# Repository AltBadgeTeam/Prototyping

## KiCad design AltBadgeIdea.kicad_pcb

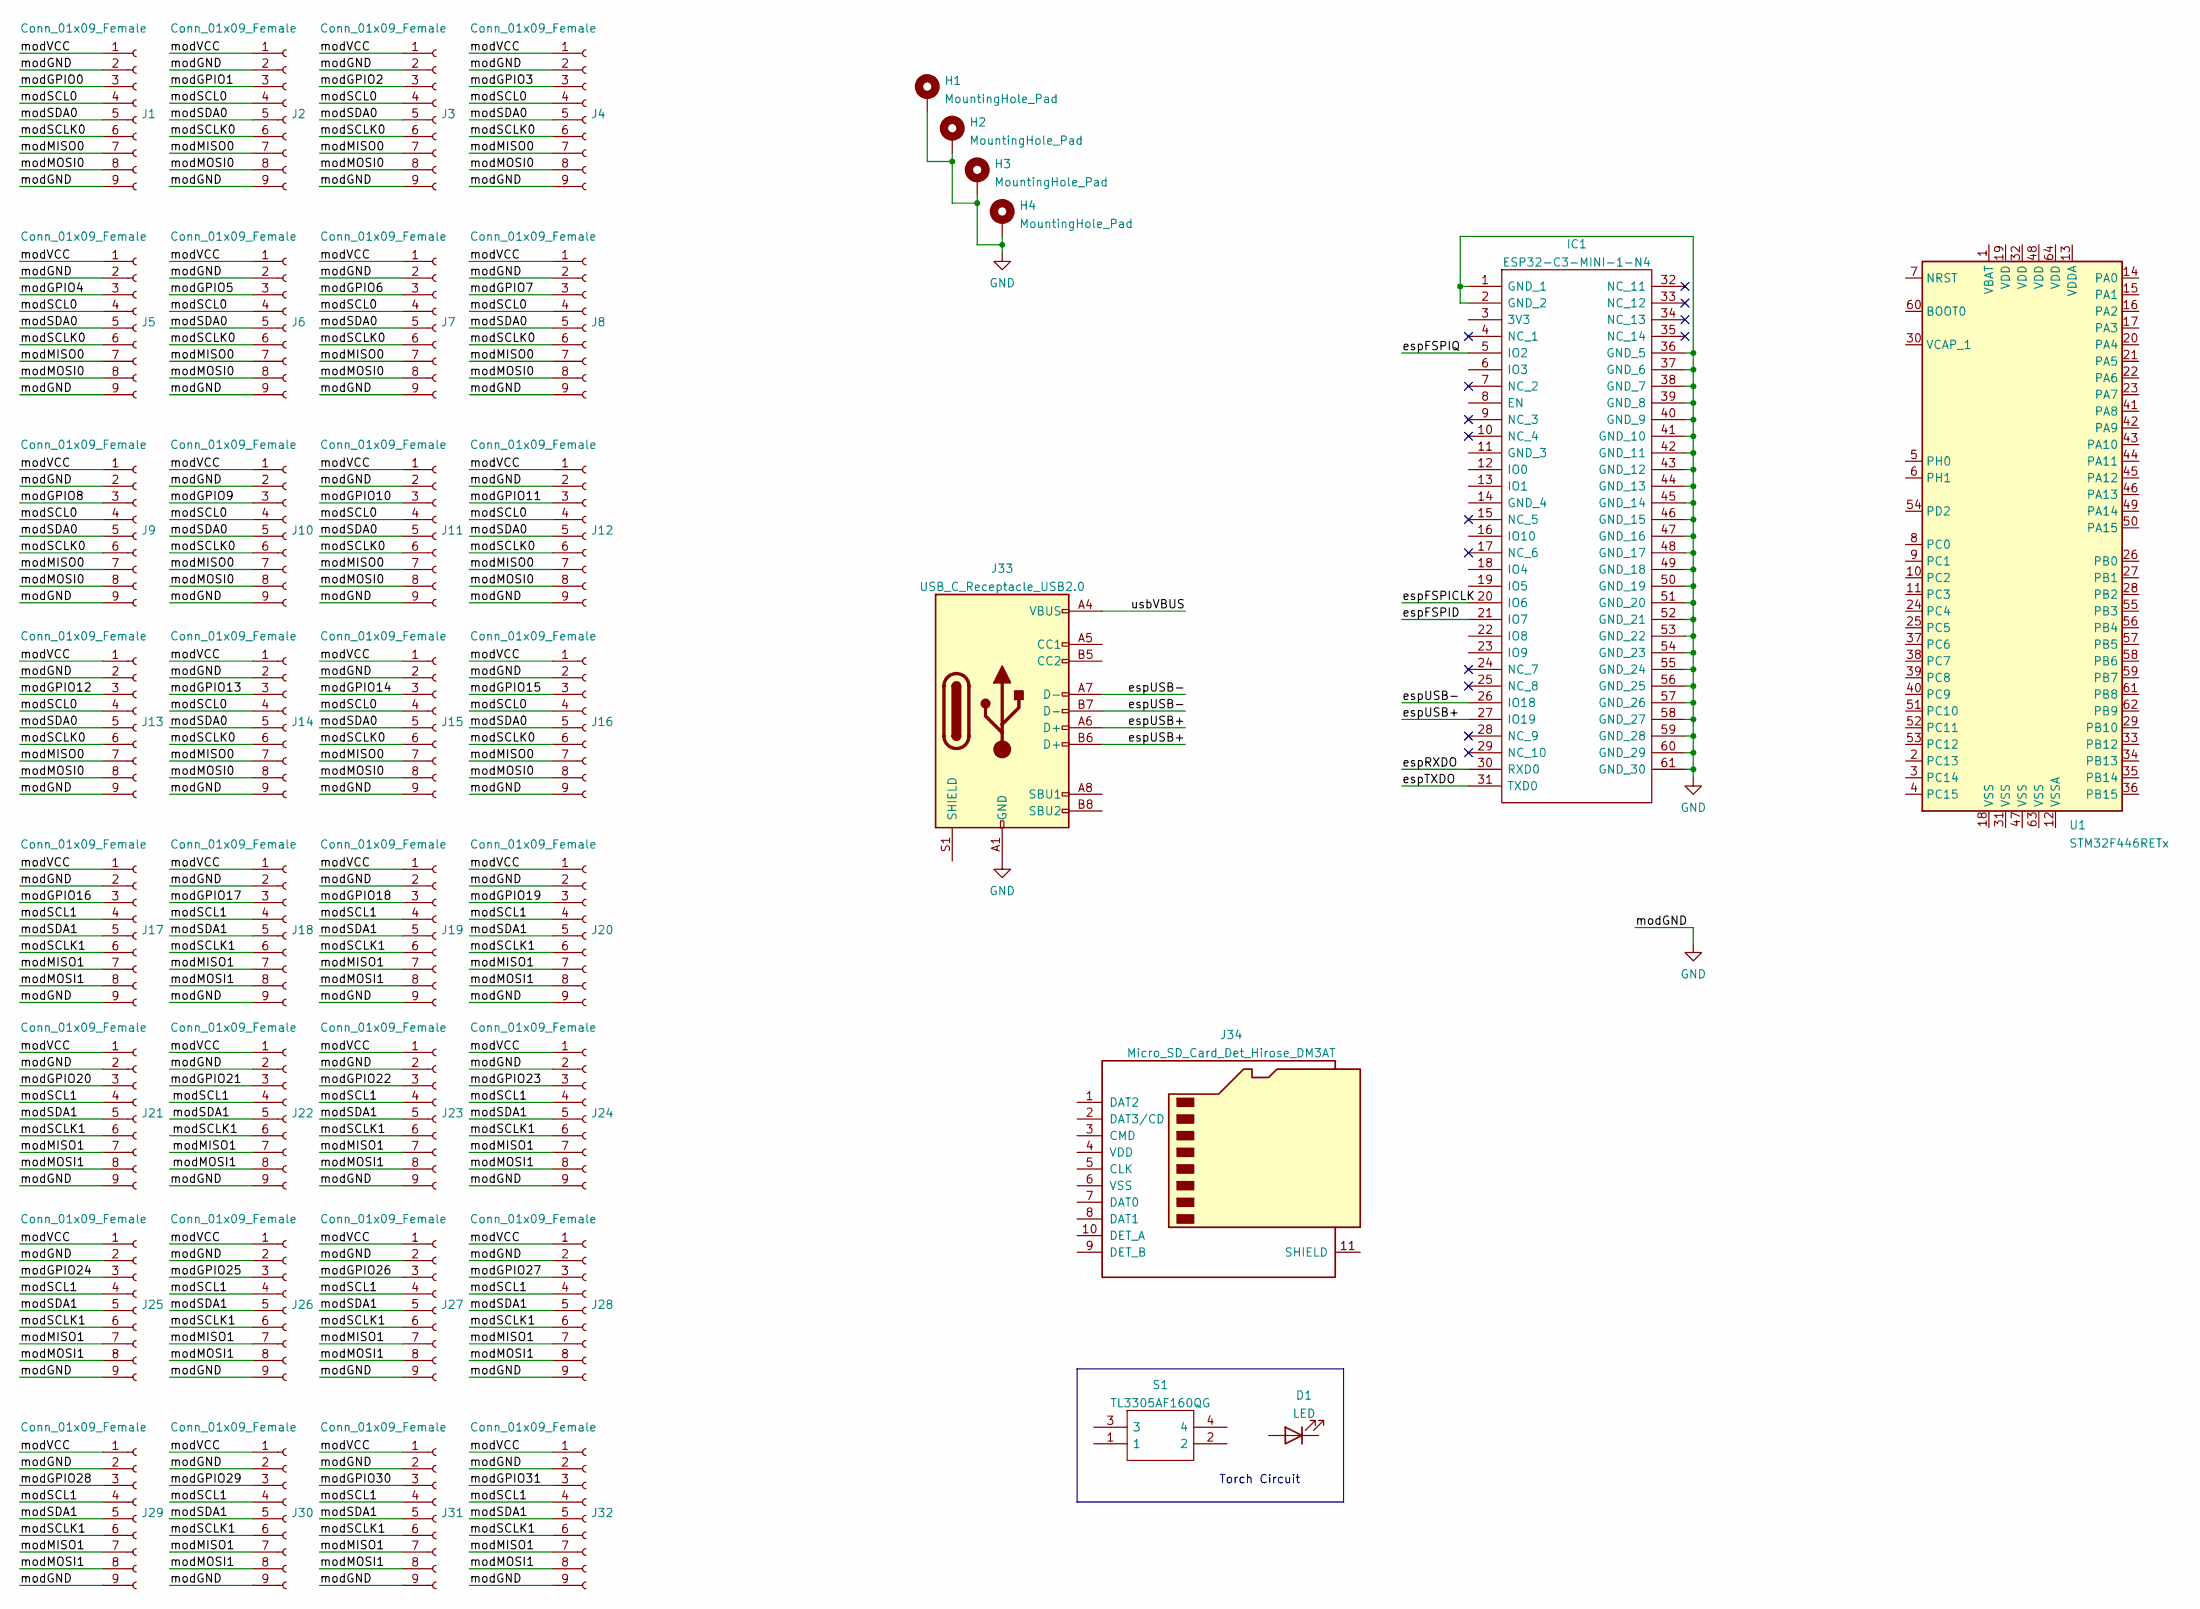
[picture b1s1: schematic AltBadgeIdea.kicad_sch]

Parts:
D1: LED; LED_D5.0mm_Horizontal_O1.27mm_Z3.0mm_Clear
H1, H2, H3, H4: MountingHole_Pad; MountingHole_5mm_Pad
IC1: ESP32-C3-MINI-1-N4; ESP32C3MINI1N4; Manufacturer_Part_Number ESP32-C3-MINI-1-N4; Mouser Part Number 356-ESP32-C3-MINI1N4
J1, J2, J3, J4, J5, J6, J7, J8, J9, J10, J11, J12, J13, J14, J15, J16, J17, J18, J19, J20, J21, J22, J23, J24, J25, J26, J27, J28, J29, J30, J31, J32: Conn_01x09_Female; PinSocket_1x09_P2.54mm_Vertical
J33: USB_C_Receptacle_USB2.0; USB_C_Receptacle_HRO_TYPE-C-31-M-12
J34: Micro_SD_Card_Det_Hirose_DM3AT; microSD_HC_Hirose_DM3AT-SF-PEJM5
S1: TL3305AF160QG; Manufacturer_Part_Number TL3305AF160QG; Mouser Part Number 612-TL3305AF160QG
U1: STM32F446RETx; LQFP-64_10x10mm_P0.5mm

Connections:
/espFSPICLK: IC1.20 (IO6)
/espFSPID: IC1.21 (IO7)
/espFSPIQ: IC1.5 (IO2)
/espRXDO: IC1.30 (RXD0)
/espTXDO: IC1.31 (TXD0)
/espUSB+: IC1.27 (IO19), J33.A6 (D+), J33.B6 (D+)
/espUSB-: IC1.26 (IO18), J33.A7 (D-), J33.B7 (D-)
/modGPIO0: J1.3
/modGPIO1: J2.3
/modGPIO2: J3.3
/modGPIO3: J4.3
/modGPIO4: J5.3
/modGPIO5: J6.3
/modGPIO6: J7.3
/modGPIO7: J8.3
/modGPIO8: J9.3
/modGPIO9: J10.3
/modGPIO10: J11.3
/modGPIO11: J12.3
/modGPIO12: J13.3
/modGPIO13: J14.3
/modGPIO14: J15.3
/modGPIO15: J16.3
/modGPIO16: J17.3
/modGPIO17: J18.3
/modGPIO18: J19.3
/modGPIO19: J20.3
/modGPIO20: J21.3
/modGPIO21: J22.3
/modGPIO22: J23.3
/modGPIO23: J24.3
/modGPIO24: J25.3
/modGPIO25: J26.3
/modGPIO26: J27.3
/modGPIO27: J28.3
/modGPIO28: J29.3
/modGPIO29: J30.3
/modGPIO30: J31.3
/modGPIO31: J32.3
/modMISO0: J1.7, J2.7, J3.7, J4.7, J5.7, J6.7, J7.7, J8.7, J9.7, J10.7, J11.7, J12.7, J13.7, J14.7, J15.7, J16.7
/modMISO1: J17.7, J18.7, J19.7, J20.7, J21.7, J22.7, J23.7, J24.7, J25.7, J26.7, J27.7, J28.7, J29.7, J30.7, J31.7, J32.7
/modMOSI0: J1.8, J2.8, J3.8, J4.8, J5.8, J6.8, J7.8, J8.8, J9.8, J10.8, J11.8, J12.8, J13.8, J14.8, J15.8, J16.8
/modMOSI1: J17.8, J18.8, J19.8, J20.8, J21.8, J22.8, J23.8, J24.8, J25.8, J26.8, J27.8, J28.8, J29.8, J30.8, J31.8, J32.8
/modSCL0: J1.4, J2.4, J3.4, J4.4, J5.4, J6.4, J7.4, J8.4, J9.4, J10.4, J11.4, J12.4, J13.4, J14.4, J15.4, J16.4
/modSCL1: J17.4, J18.4, J19.4, J20.4, J21.4, J22.4, J23.4, J24.4, J25.4, J26.4, J27.4, J28.4, J29.4, J30.4, J31.4, J32.4
/modSCLK0: J1.6, J2.6, J3.6, J4.6, J5.6, J6.6, J7.6, J8.6, J9.6, J10.6, J11.6, J12.6, J13.6, J14.6, J15.6, J16.6
/modSCLK1: J17.6, J18.6, J19.6, J20.6, J21.6, J22.6, J23.6, J24.6, J25.6, J26.6, J27.6, J28.6, J29.6, J30.6, J31.6, J32.6
/modSDA0: J1.5, J2.5, J3.5, J4.5, J5.5, J6.5, J7.5, J8.5, J9.5, J10.5, J11.5, J12.5, J13.5, J14.5, J15.5, J16.5
/modSDA1: J17.5, J18.5, J19.5, J20.5, J21.5, J22.5, J23.5, J24.5, J25.5, J26.5, J27.5, J28.5, J29.5, J30.5, J31.5, J32.5
/modVCC: J1.1, J2.1, J3.1, J4.1, J5.1, J6.1, J7.1, J8.1, J9.1, J10.1, J11.1, J12.1, J13.1, J14.1, J15.1, J16.1, J17.1, J18.1, J19.1, J20.1, J21.1, J22.1, J23.1, J24.1, J25.1, J26.1, J27.1, J28.1, J29.1, J30.1, J31.1, J32.1
/usbVBUS: J33.A4 (VBUS), J33.A9 (VBUS), J33.B4 (VBUS), J33.B9 (VBUS)
GND: H1.1, H2.1, H3.1, H4.1, IC1.1 (GND_1), IC1.2 (GND_2), IC1.36 (GND_5), IC1.37 (GND_6), IC1.38 (GND_7), IC1.39 (GND_8), IC1.40 (GND_9), IC1.41 (GND_10), IC1.42 (GND_11), IC1.43 (GND_12), IC1.44 (GND_13), IC1.45 (GND_14), IC1.46 (GND_15), IC1.47 (GND_16), IC1.48 (GND_17), IC1.49 (GND_18), IC1.50 (GND_19), IC1.51 (GND_20), IC1.52 (GND_21), IC1.53 (GND_22), IC1.54 (GND_23), IC1.55 (GND_24), IC1.56 (GND_25), IC1.57 (GND_26), IC1.58 (GND_27), IC1.59 (GND_28), IC1.60 (GND_29), IC1.61 (GND_30), J1.2, J1.9, J2.2, J2.9, J3.2, J3.9, J4.2, J4.9, J5.2, J5.9, J6.2, J6.9, J7.2, J7.9, J8.2, J8.9, J9.2, J9.9, J10.2, J10.9, J11.2, J11.9, J12.2, J12.9, J13.2, J13.9, J14.2, J14.9, J15.2, J15.9, J16.2, J16.9, J17.2, J17.9, J18.2, J18.9, J19.2, J19.9, J20.2, J20.9, J21.2, J21.9, J22.2, J22.9, J23.2, J23.9, J24.2, J24.9, J25.2, J25.9, J26.2, J26.9, J27.2, J27.9, J28.2, J28.9, J29.2, J29.9, J30.2, J30.9, J31.2, J31.9, J32.2, J32.9, J33.A1 (GND), J33.A12 (GND), J33.B1 (GND), J33.B12 (GND)

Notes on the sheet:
Torch Circuit

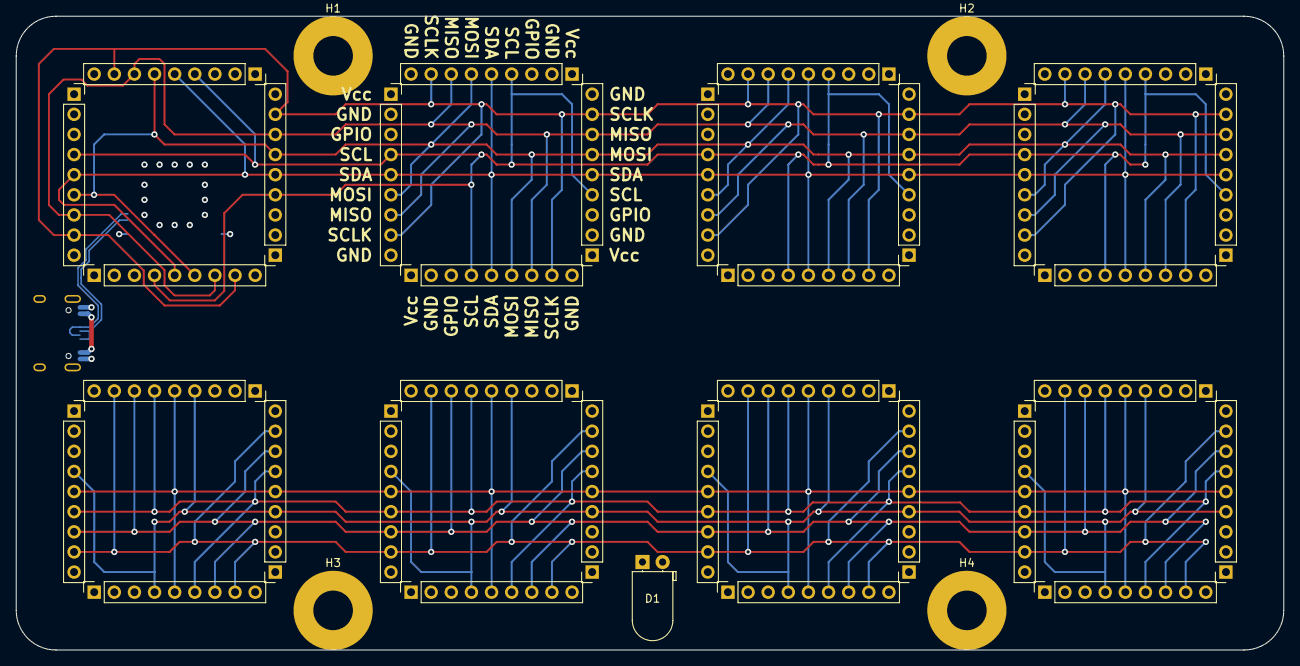
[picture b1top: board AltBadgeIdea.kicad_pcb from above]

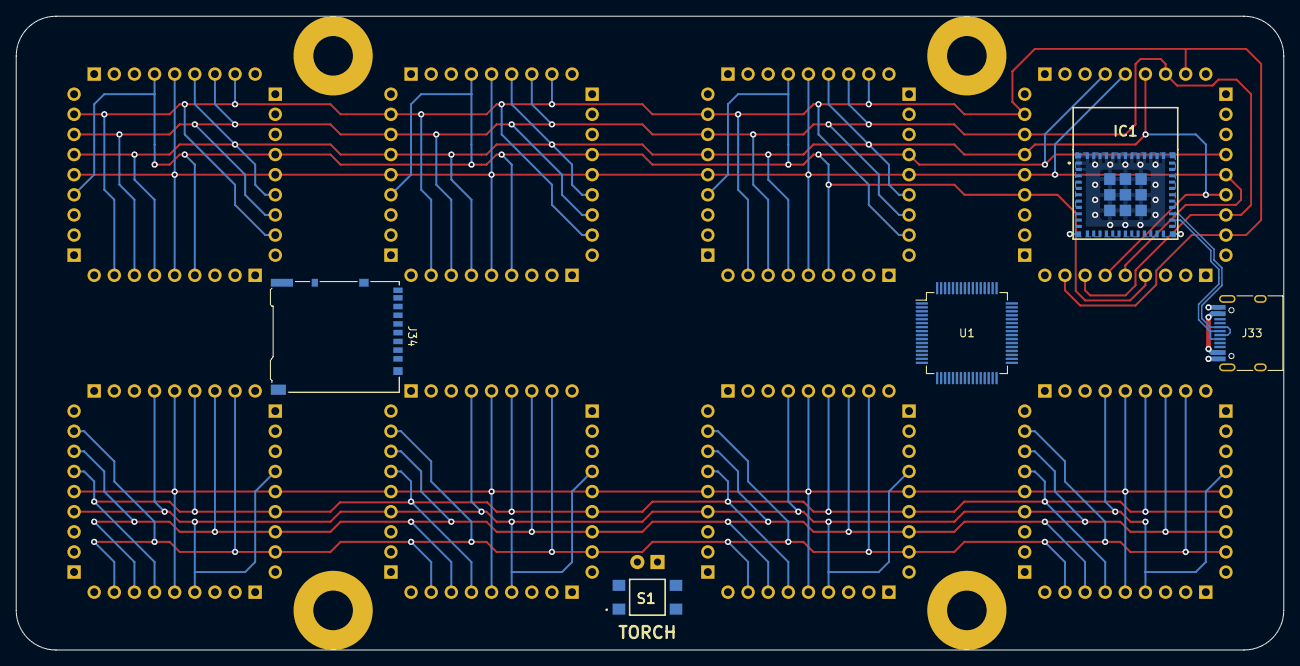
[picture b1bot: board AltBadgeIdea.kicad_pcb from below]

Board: 4 copper layers, 160.0 x 80.0 mm, 42 parts (5 on the bottom side), 15 nets.

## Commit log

2023-01-24 Initial badge from Laurence
2023-01-24 Removed old zip of project
2023-01-28 Added badglet templates
